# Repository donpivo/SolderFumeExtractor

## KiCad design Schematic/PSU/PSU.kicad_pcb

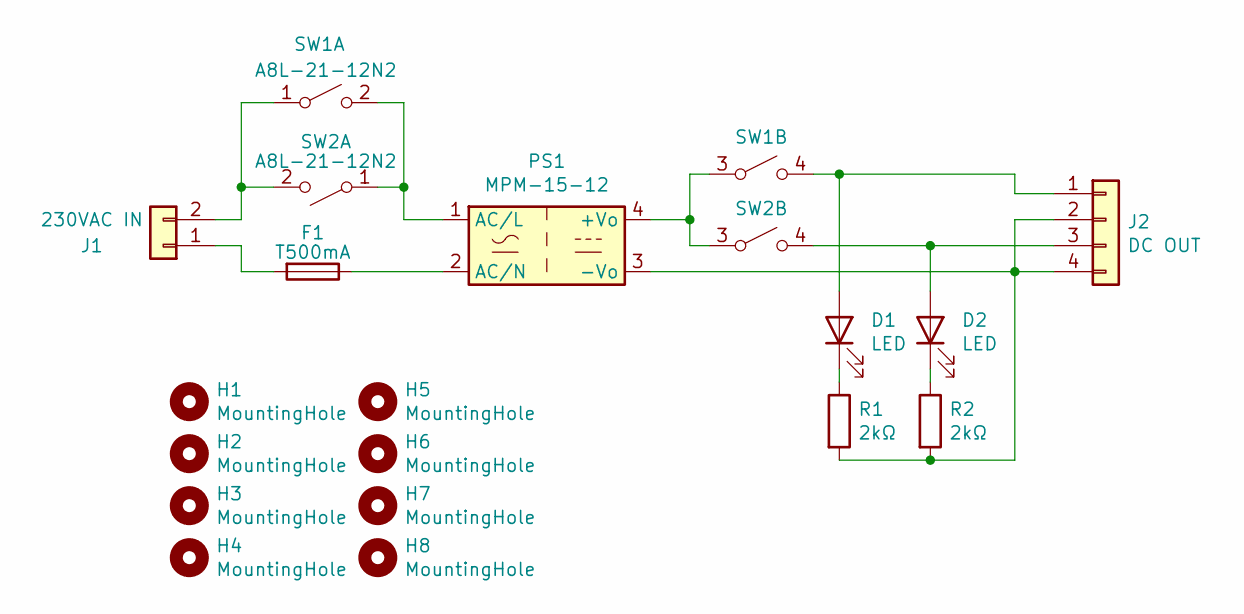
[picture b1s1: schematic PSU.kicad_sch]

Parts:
D1, D2: LED; LED_D3.0mm
F1: T500mA; Fuse_Littelfuse_372_D8.50mm
H1, H2, H3, H4, H5, H6, H7, H8: MountingHole; MountingHole_3.2mm_M3
J1: 230VAC IN; TerminalBlock_LCSC_P5.08mm
J2: DC OUT; PinHeader_1x04_P2.54mm_Vertical
PS1: MPM-15-12; Converter_ACDC_MeanWell_IRM-20-xx_THT
R1, R2: 2kΩ; R_0805_2012Metric_Pad1.20x1.40mm_HandSolder
SW1, SW2: A8L-21-12N2; Switch_rocker_DPST

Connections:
unnamed: D1.1 (K), R1.1
unnamed: D1.2 (A), J2.1, SW1.4 (B)
unnamed: D2.1 (K), R2.1
unnamed: D2.2 (A), J2.3, SW2.4 (B)
unnamed: F1.1, PS1.2 (AC/N)
unnamed: F1.2, J1.1
unnamed: J1.2, SW1.1 (A), SW2.2 (B)
unnamed: J2.2, J2.4, PS1.3 (-Vo), R1.2, R2.2
unnamed: PS1.1 (AC/L), SW1.2 (B), SW2.1 (A)
unnamed: PS1.4 (+Vo), SW1.3 (A), SW2.3 (A)

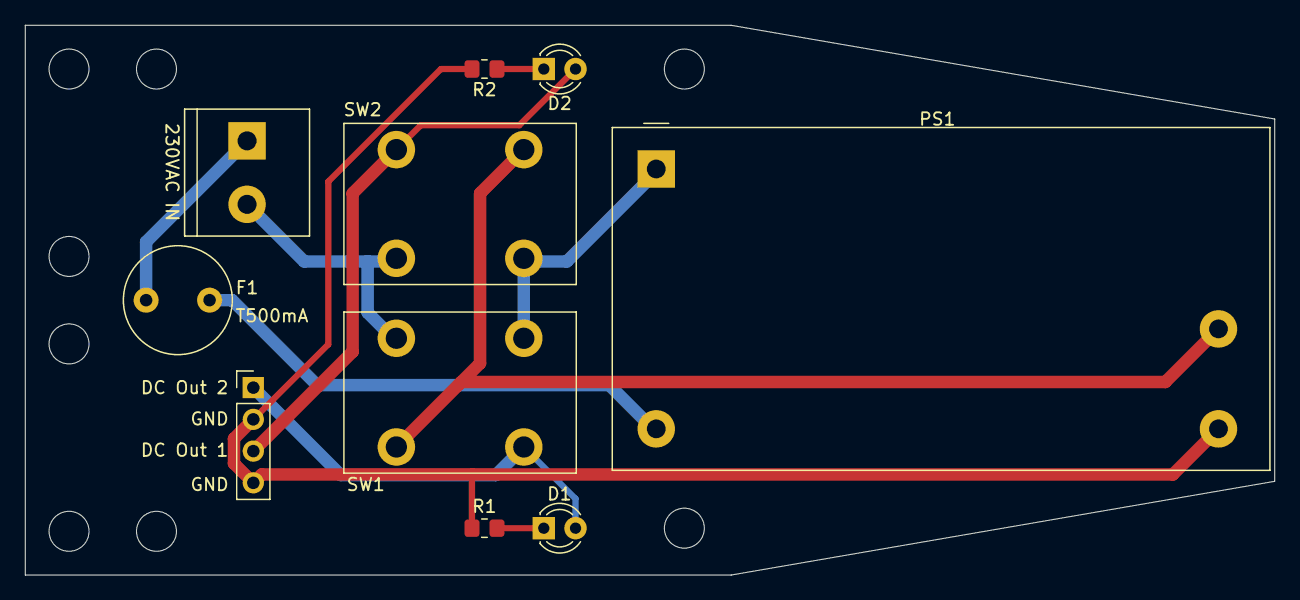
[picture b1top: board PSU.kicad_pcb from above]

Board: 2 copper layers, 100.0 x 44.0 mm, 18 parts (0 on the bottom side), 10 nets.

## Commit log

2023-07-07 Added inlay for slightly smaller filters
